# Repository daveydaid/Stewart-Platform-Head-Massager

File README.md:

# Stewart-Gough Robotic Platform

# Detailed Blog Post: 

https://davidmcdaid.wordpress.com/2022/08/03/stewart-platform-head-massager/

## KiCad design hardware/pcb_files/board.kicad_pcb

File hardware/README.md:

# Arduino Mega2560 Compatible PCB

# Refer to Detailed Blog Post: 

[https://davidmcdaid.wordpress.com/](https://davidmcdaid.wordpress.com/)

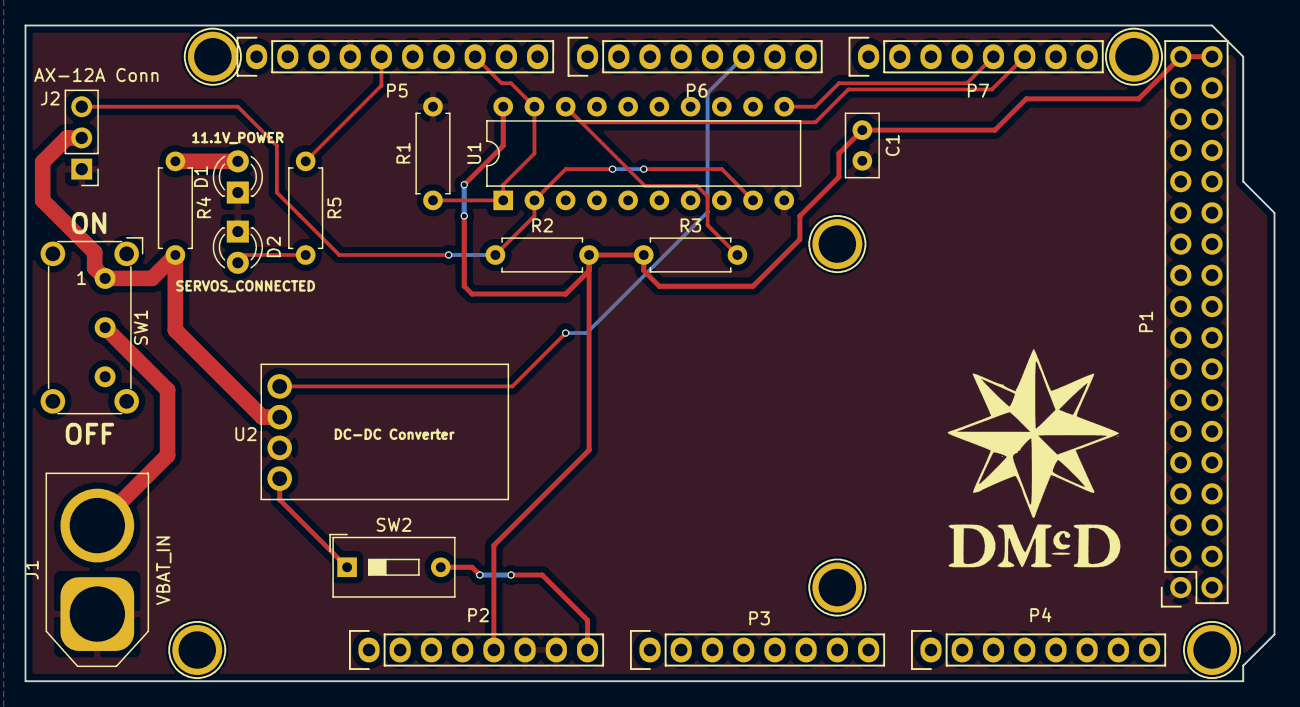
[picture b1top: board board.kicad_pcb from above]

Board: 2 copper layers, 101.6 x 53.3 mm, 27 parts (0 on the bottom side), 14 nets.

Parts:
C1: 0.1uF; C_Disc_D5.0mm_W2.5mm_P2.50mm
D1: LED; LED_D3.0mm
D2: ATTACHED; LED_D3.0mm
J1: VBAT_IN; AMASS_XT60-M_1x02_P7.20mm_Vertical
J2: AX-12A Conn; PinHeader_1x03_P2.54mm_Vertical
P1: Digital; Socket_Strip_Arduino_2x18
P2: Power; Socket_Strip_Arduino_1x08
P3, P4: Analog; Socket_Strip_Arduino_1x08
P5: PWM; Socket_Strip_Arduino_1x10
P6: PWM; Socket_Strip_Arduino_1x08
P7: Communication; Socket_Strip_Arduino_1x08
P8, P9, P10, P11, P12, P13: CONN_01X01; Arduino_1pin
R1, R2, R3: 10K; R_Axial_DIN0207_L6.3mm_D2.5mm_P7.62mm_Horizontal
R4, R5: value needs calcd; R_Axial_DIN0207_L6.3mm_D2.5mm_P7.62mm_Horizontal
SW1: SW_DIP_x01; SW_E-Switch_EG1224_SPDT_Angled
SW2: SW_DIP_x01; SW_DIP_SPSTx01_Slide_9.78x4.72mm_W7.62mm_P2.54mm
U1: SN74HC241N; DIP-20_W7.62mm
U2: DC_DC_Step_Down_YOUMILE

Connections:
+5V: C1.1, P1.35, P1.36, P2.5, R2.2, R3.1, U1.20
/2(**): P6.6, U2.1
/10(**): P5.8, R1.1, U1.1, U1.19
/13(**): P5.5, R5.1
/18(Tx1): P7.5, U1.11
/19(Rx1): P7.6, R3.2, U1.18
/Vin: P2.8, SW2.2
GND: C1.2, D1.1, D2.1, J1.1, J2.1, P1.1, P1.2, P2.6, P2.7, P5.4, R1.2, U1.10, U2.3
unnamed: D1.2, R4.1
unnamed: D2.2, R5.2
unnamed: J1.2, SW1.2
unnamed: J2.2, R4.2, SW1.1, U2.2
unnamed: J2.3, R2.1, U1.2, U1.9
unnamed: SW2.1, U2.4

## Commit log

2022-03-24 Initial repo post
2022-07-09 v2.0 Release
    - Created new hardware platform
    - Updated and cleaned Arduino source
2022-08-03 v2.1 Release
    - Cleaned source
    - New gif
    - Added missing 3D print files
2022-08-03 Create LICENSE
2023-02-08 Naming fix
    Fixing PCB 3D file name
